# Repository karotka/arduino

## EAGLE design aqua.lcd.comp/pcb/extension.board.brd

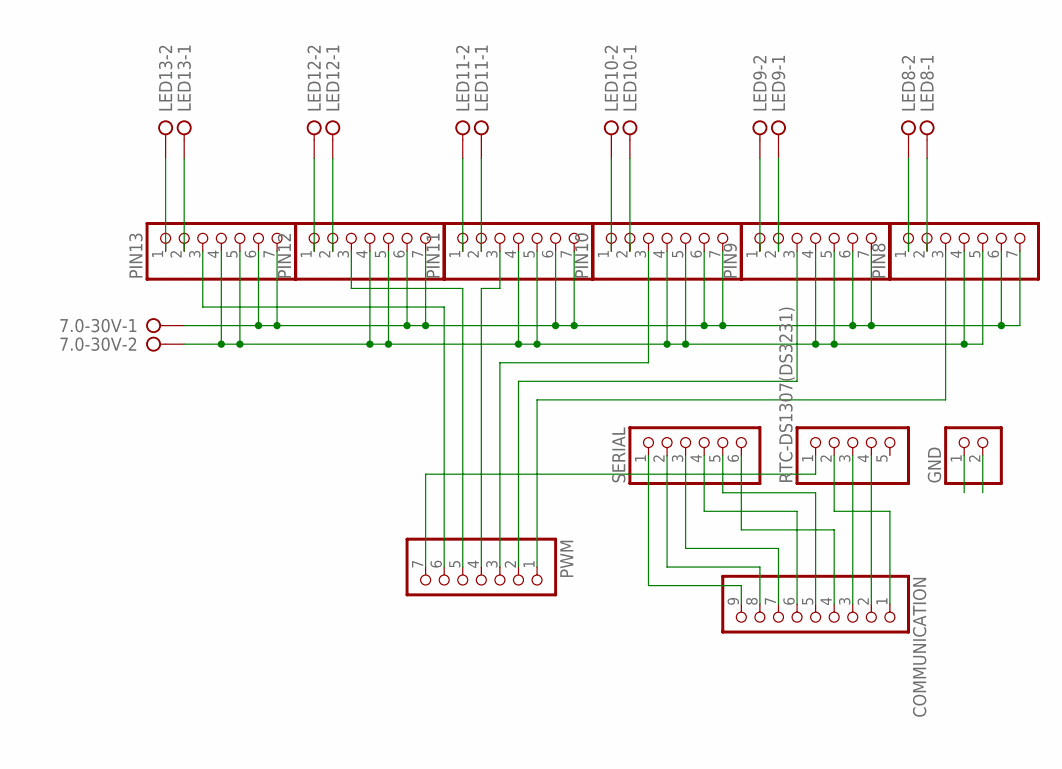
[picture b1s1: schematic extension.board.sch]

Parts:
7.0-30V: W237-02P; W237-132
COMMUNICATION: PINHD-1X9; 1X09
GND: PINHD-1X2; 1X02
LED8, LED9, LED10, LED11, LED12, LED13: W237-02P; W237-132
PIN8, PIN9, PIN10, PIN11, PIN12, PIN13: PINHD-1X7; 1X07
PWM: PINHD-1X7; 1X07
RTC-DS1307(DS3231): PINHD-1X5; 1X05
SERIAL: PINHD-1X6; 1X06

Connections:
GND: 7.0-30V.2, GND.1, PIN8.4, PIN8.5, PIN9.4, PIN9.5, PIN10.4, PIN10.5, PIN11.4, PIN11.5, PIN12.4, PIN12.5, PIN13.4, PIN13.5, PWM.7, RTC-DS1307(DS3231).1
unnamed: COMMUNICATION.2, RTC-DS1307(DS3231).4
unnamed: COMMUNICATION.3, RTC-DS1307(DS3231).3
unnamed: COMMUNICATION.4, SERIAL.6
unnamed: COMMUNICATION.5, SERIAL.5
unnamed: PIN8.3, PWM.1
unnamed: PIN9.3, PWM.2
unnamed: PIN10.3, PWM.3
unnamed: PIN11.3, PWM.4
unnamed: PIN12.3, PWM.5
unnamed: PIN13.3, PWM.6
unnamed: LED8.1, PIN8.2
unnamed: LED8.2, PIN8.1
unnamed: LED9.1, PIN9.2
unnamed: LED9.2, PIN9.1
unnamed: LED10.1, PIN10.2
unnamed: LED10.2, PIN10.1
unnamed: LED11.1, PIN11.2
unnamed: LED11.2, PIN11.1
unnamed: LED12.1, PIN12.2
unnamed: LED12.2, PIN12.1
unnamed: LED13.1, PIN13.2
unnamed: LED13.2, PIN13.1
unnamed: COMMUNICATION.6, SERIAL.4
unnamed: COMMUNICATION.7, SERIAL.3
unnamed: COMMUNICATION.8, SERIAL.2
unnamed: COMMUNICATION.9, SERIAL.1
VCC: COMMUNICATION.1, GND.2, RTC-DS1307(DS3231).2
VCC12: 7.0-30V.1, PIN8.6, PIN8.7, PIN9.6, PIN9.7, PIN10.6, PIN10.7, PIN11.6, PIN11.7, PIN12.6, PIN12.7, PIN13.6, PIN13.7

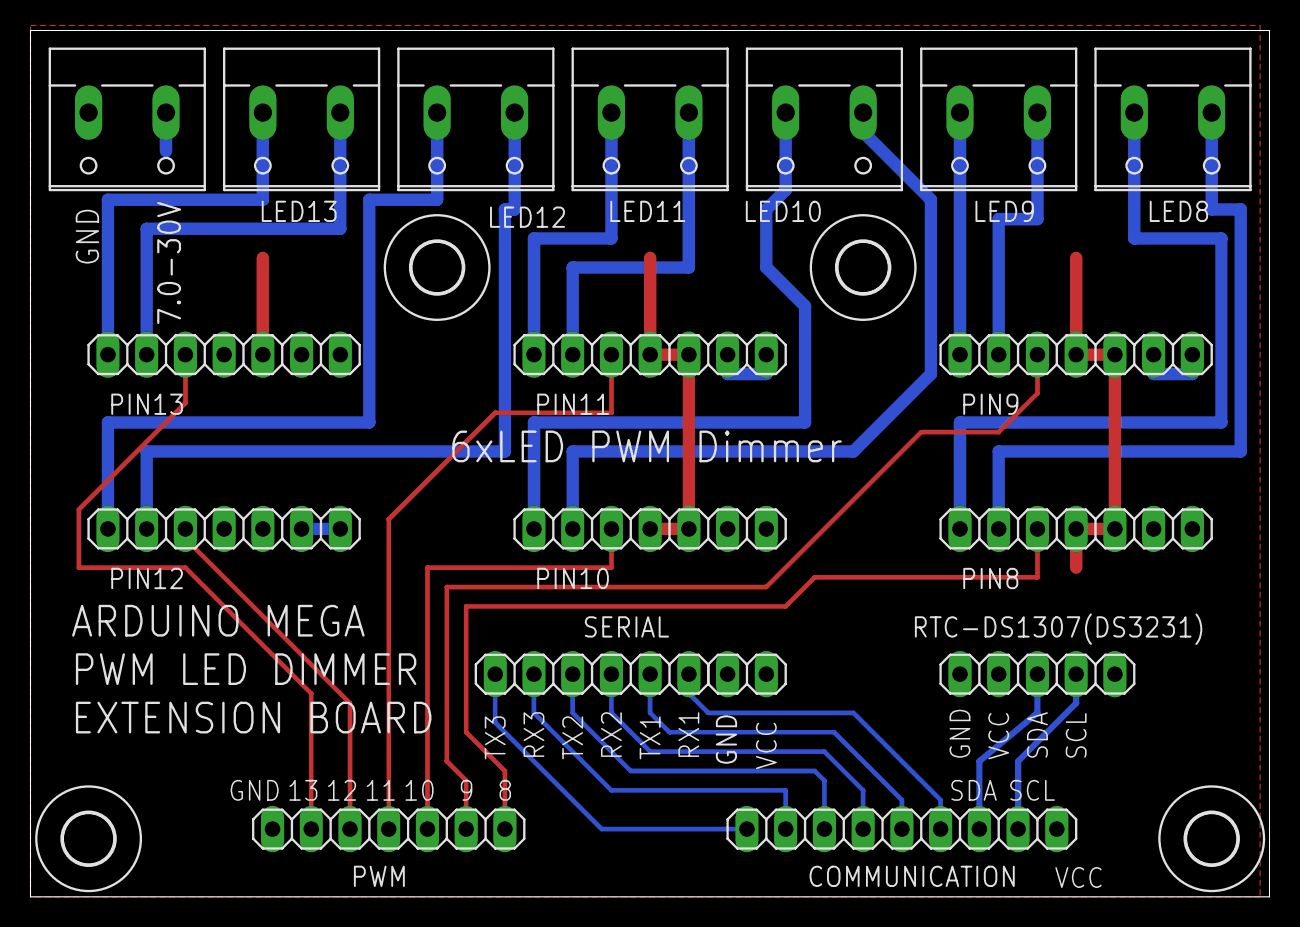
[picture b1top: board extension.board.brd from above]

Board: 2 copper layers, 81.3 x 56.8 mm, 22 parts (0 on the bottom side), 29 nets.

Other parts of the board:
U$1, U$2, U$3, U$4: 3,3

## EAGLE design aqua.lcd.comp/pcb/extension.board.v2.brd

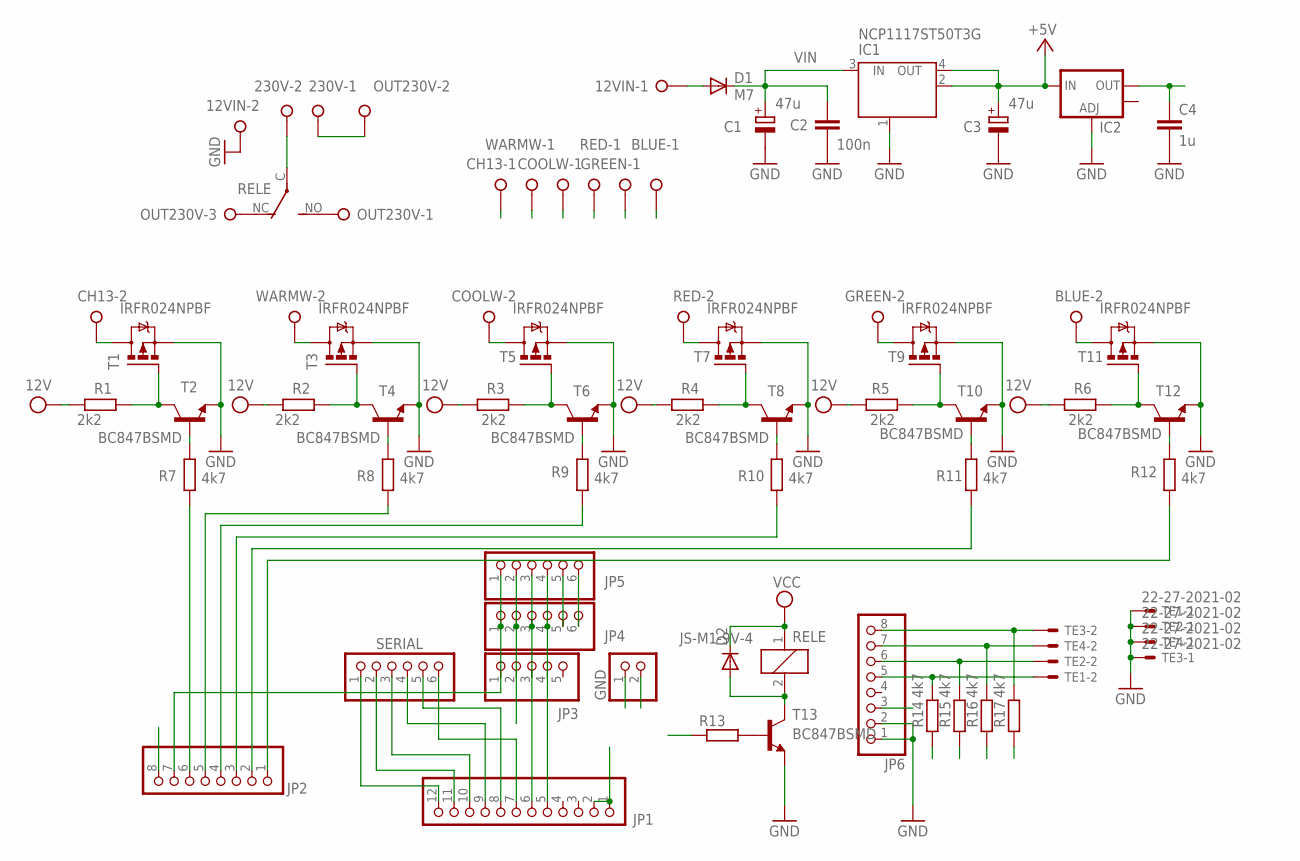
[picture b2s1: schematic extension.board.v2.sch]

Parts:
12VIN, 230V: W237-02P; W237-132
BLUE: W237-02P; W237-132
C1, C3: 47u; PANASONIC_D
C2: 100n; C1206
C4: 1u; C0805
CH13: W237-02P; W237-132
COOLW: W237-02P; W237-132
D1: M7; SMB
D2: DIODE-DO-214AC; DO-214AC
GND: PINHD-1X2; 1X02
GREEN: W237-02P; W237-132
IC1: NCP1117ST50T3G; SOT223
IC2: V_REG_LM1117SOT223; SOT223
JP1: PINHD-1X12; 1X12
JP2, JP6: PINHD-1X8; 1X08
JP3: PINHD-1X5; 1X05
JP4, JP5: PINHD-1X6; 1X06
OUT230V: W237-3E
R1, R2, R3, R4, R5, R6: 2k2; R1206
R7, R8, R9, R10, R11, R12, R14, R15, R16, R17: 4k7; R1206
R13: R-EU_0207/15; 0207/15
RED: W237-02P; W237-132
RELE: JS-M1-9V-4; JS-M
SERIAL: PINHD-1X6; 1X06
T1, T3, T5, T7, T9, T11: IRFR024NPBF; D-PAK_TO252AA
T2, T4, T6, T8, T10, T12, T13: BC847BSMD; SOT23
TE1, TE2, TE3, TE4: 22-27-2021-02; 6410-02
WARMW: W237-02P; W237-132

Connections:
3.3V: C4.1, IC2.2 (OUT), JP2.8, JP3.2, JP4.2, JP5.2, R14.2, R15.2, R16.2, R17.2
+5V: C3.+, D2.C, GND.2, IC1.2 (OUT), IC1.4 (OUT), IC2.3 (IN), JP1.1, JP1.2, RELE.1
GND: 12VIN.2, C1.-, C2.2, C3.-, C4.2, GND.1, IC1.1 (GND/ADJ), IC2.1 (ADJ), JP2.7, JP3.1, JP4.1, JP5.1, JP6.1, JP6.2, T1.3 (S), T2.2 (E), T3.3 (S), T4.2 (E), T5.3 (S), T6.2 (E), T7.3 (S), T8.2 (E), T9.3 (S), T10.2 (E), T11.3 (S), T12.2 (E), T13.2 (E), TE1.1, TE2.1, TE3.1, TE4.1
unnamed: 230V.1, OUT230V.2
unnamed: 230V.2, RELE.C
unnamed: JP1.7, SERIAL.6
unnamed: JP1.8, SERIAL.5
unnamed: JP2.1, R12.2
unnamed: JP2.2, R11.2
unnamed: JP2.3, R10.2
unnamed: JP2.4, R9.2
unnamed: JP2.5, R8.2
unnamed: JP2.6, R7.2
unnamed: R7.1, T2.1 (B)
unnamed: R1.2, T1.1 (G), T2.3 (C)
unnamed: CH13.2, T1.4 (D)
unnamed: OUT230V.1, RELE.NO (S)
unnamed: R8.1, T4.1 (B)
unnamed: R2.2, T3.1 (G), T4.3 (C)
unnamed: T3.4 (D), WARMW.2
unnamed: R9.1, T6.1 (B)
unnamed: R3.2, T5.1 (G), T6.3 (C)
unnamed: COOLW.2, T5.4 (D)
unnamed: R10.1, T8.1 (B)
unnamed: R4.2, T7.1 (G), T8.3 (C)
unnamed: JP1.9, SERIAL.4
unnamed: JP1.10, SERIAL.3
unnamed: JP1.11, SERIAL.2
unnamed: JP6.8, R17.1, TE3.2
unnamed: RED.2, T7.4 (D)
unnamed: R11.1, T10.1 (B)
unnamed: R5.2, T9.1 (G), T10.3 (C)
unnamed: GREEN.2, T9.4 (D)
unnamed: R12.1, T12.1 (B)
unnamed: R6.2, T11.1 (G), T12.3 (C)
unnamed: BLUE.2, T11.4 (D)
unnamed: R13.2, T13.1 (B)
unnamed: OUT230V.3, RELE.NC (O)
unnamed: JP6.7, R16.1, TE4.2
unnamed: D2.A, RELE.2, T13.3 (C)
unnamed: JP6.5, R14.1, TE1.2
unnamed: JP6.6, R15.1, TE2.2
unnamed: JP4.5, JP5.5
unnamed: JP4.6, JP5.6
PWRIN: 12VIN.1, BLUE.1, CH13.1, COOLW.1, D1.A, GREEN.1, RED.1, WARMW.1
SCL: JP1.5, JP3.4, JP4.4, JP5.4
SDA: JP1.6, JP3.3, JP4.3, JP5.3
TX3: JP1.12, R13.1, SERIAL.1
VIN: C1.+, C2.1, D1.C, IC1.3 (IN), JP6.3, R1.1, R2.1, R3.1, R4.1, R5.1, R6.1

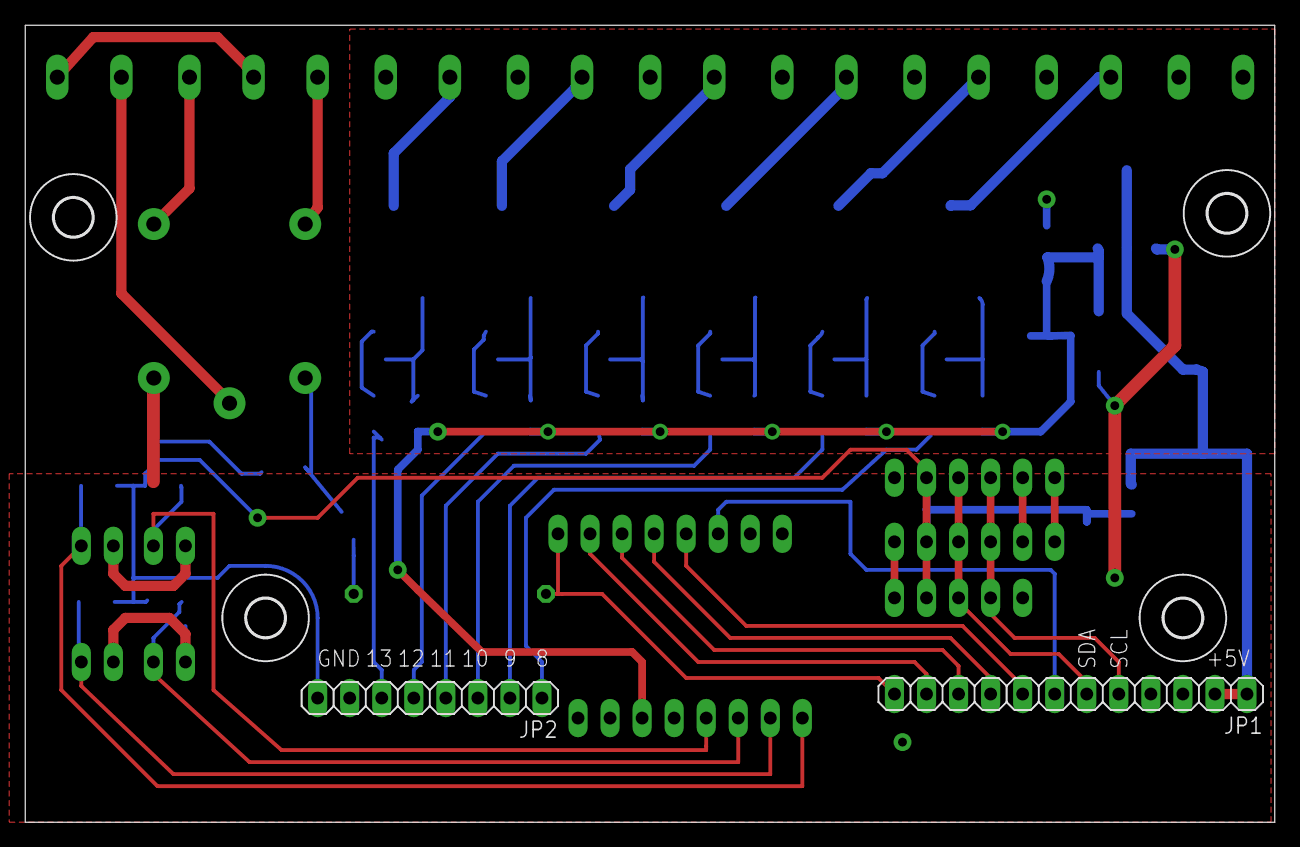
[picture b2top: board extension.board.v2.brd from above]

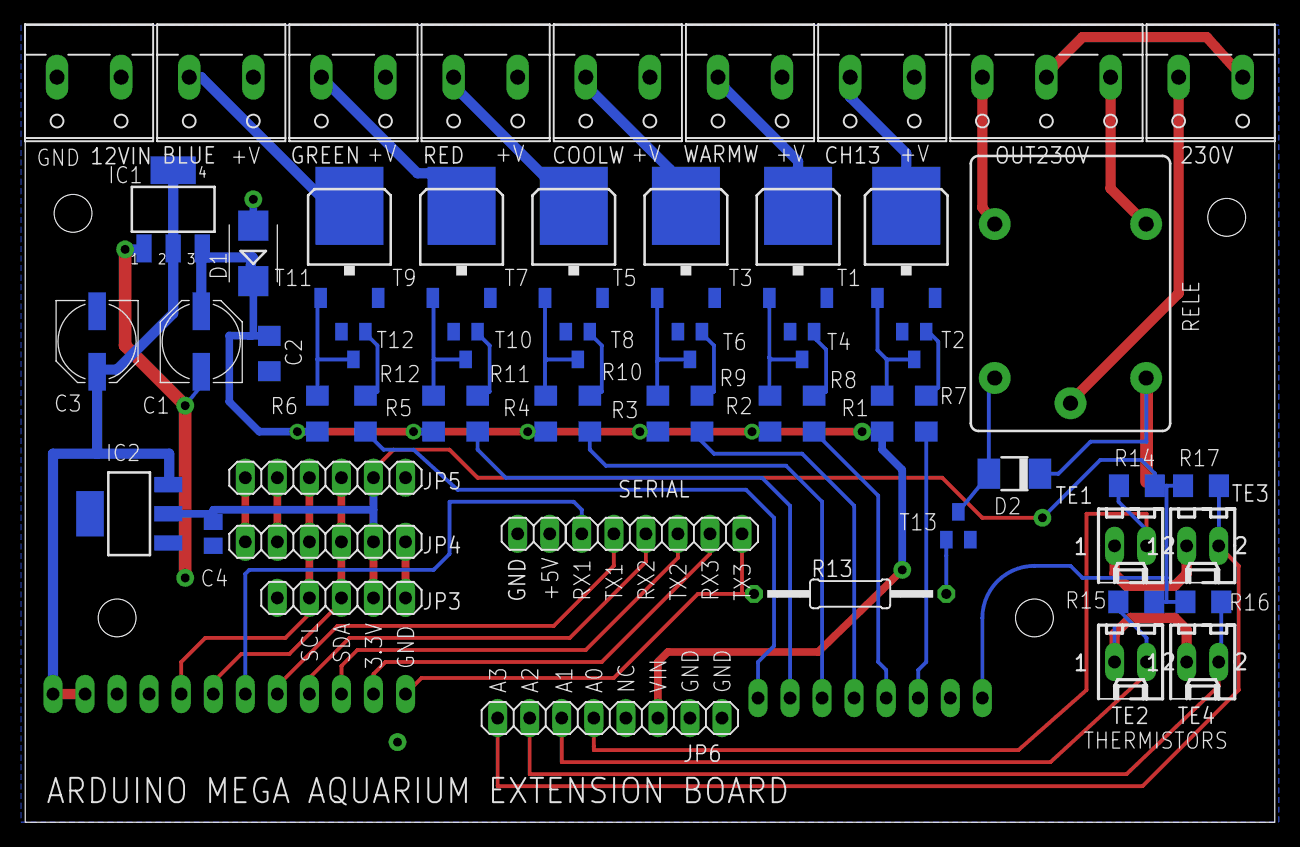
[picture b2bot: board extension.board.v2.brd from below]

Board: 2 copper layers, 99.0 x 63.2 mm, 64 parts (58 on the bottom side), 49 nets.

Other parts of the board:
U$1, U$2, U$3, U$4: 3,0

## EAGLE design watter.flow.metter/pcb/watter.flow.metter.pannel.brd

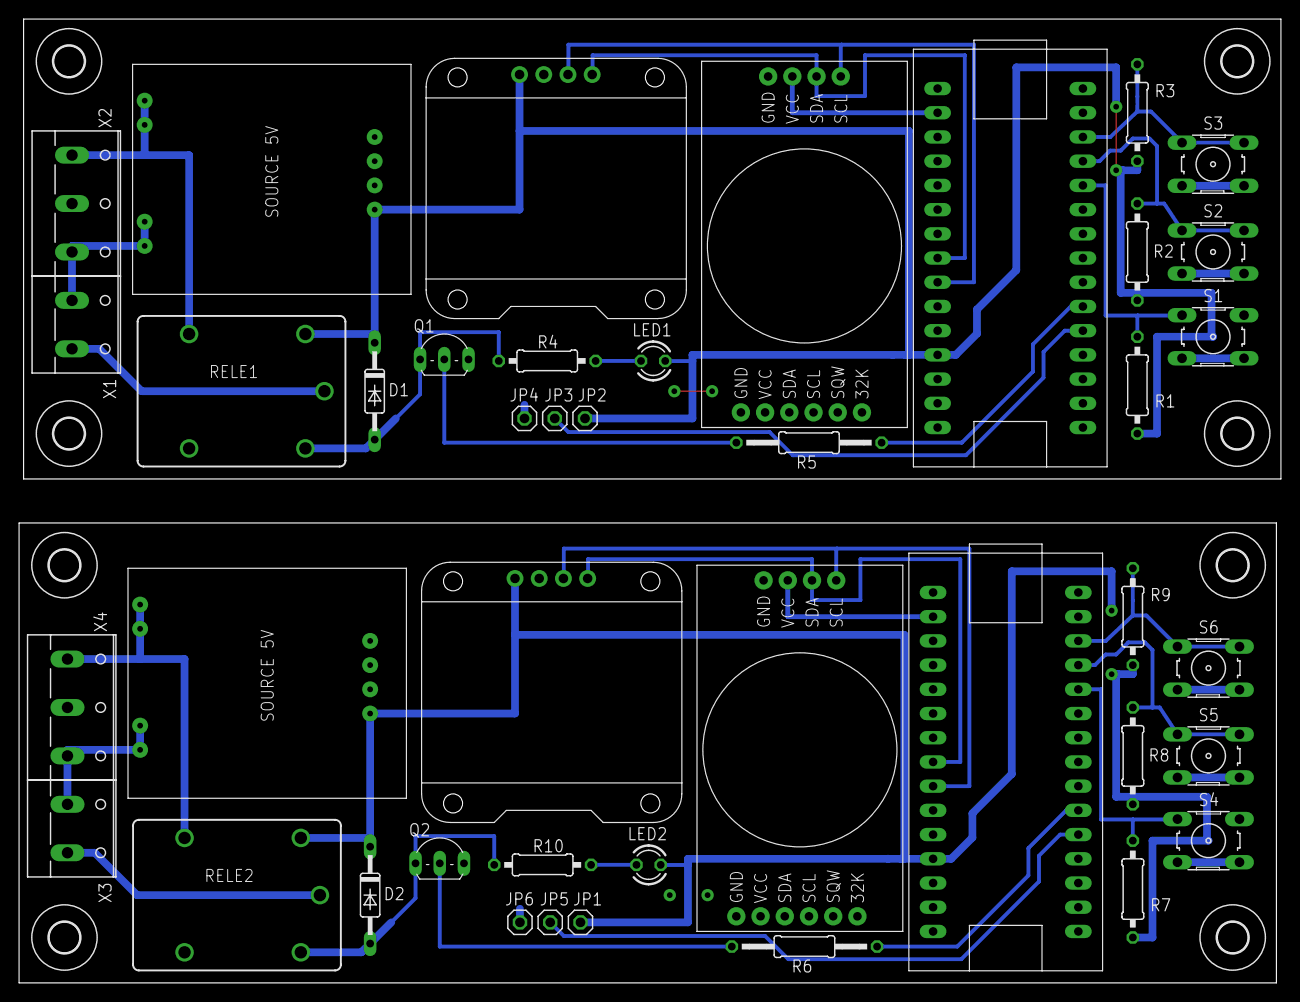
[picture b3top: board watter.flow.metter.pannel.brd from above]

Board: 2 copper layers, 132.4 x 101.1 mm, 50 parts (0 on the bottom side), 32 nets.

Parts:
D1, D2: 1N4148DO35-10; DO35-10
DISPLAY, DISPLAY1: OLED_0.96_I2C
JP1, JP2, JP3, JP4, JP5, JP6: 1X01
LED1, LED2: LED3MM
Q1, Q2: BC546A; TO92-EBC
R1, R2, R3, R4, R7, R8, R9, R10: 0207/10
R5, R6: 0207/15
RELE1, RELE2: JS-M1-9V-4; JS-M
S1, S2, S3, S4, S5, S6: B3F-10XX
U$1, U$5: NANO
U$2, U$10: PWR5V; SUPP
U$3, U$4, U$7, U$8, U$11, U$12, U$13, U$14: 3,2
U$6, U$9: DS3231BOARD; BOARD
X1, X3: W237-132
X2, X4: W237-3E

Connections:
3.3V: U$5.3.3V, U$6.VCC@2
3.3V1: U$1.3.3V, U$9.VCC@2
D1: JP5.1, U$1.D2
D2: JP3.1, U$5.D2
D3: R5.1, U$5.D3
D4: R6.1, U$1.D3
GND: DISPLAY.GND, JP4.1, Q1.E, S1.3, S1.4, S2.3, S2.4, S3.3, S3.4, U$2.P$5, U$5.GND, U$6.GND@1, U$6.GND@2
GND1: DISPLAY1.GND, JP6.1, Q2.E, S4.3, S4.4, S5.3, S5.4, S6.3, S6.4, U$1.GND, U$9.GND@1, U$9.GND@2, U$10.P$5
unnamed: RELE1.C, X1.2
unnamed: R1.1, S1.1, S1.2, U$5.D8
unnamed: U$2.P$3, U$2.P$4, X1.1, X2.3
unnamed: RELE1.NO, U$2.P$1, U$2.P$2, X2.1
unnamed: R2.1, S2.1, S2.2, U$5.D9
unnamed: R3.1, S3.1, S3.2, U$5.D10
unnamed: Q1.B, R5.2
unnamed: LED1.K, R4.2
unnamed: D2.A, Q2.C, R10.1, RELE2.2
unnamed: U$10.P$3, U$10.P$4, X3.1, X4.3
unnamed: RELE2.NO, U$10.P$1, U$10.P$2, X4.1
unnamed: RELE2.C, X3.2
unnamed: R7.1, S4.1, S4.2, U$1.D8
unnamed: R8.1, S5.1, S5.2, U$1.D9
unnamed: R9.1, S6.1, S6.2, U$1.D10
unnamed: Q2.B, R6.2
unnamed: LED2.K, R10.2
unnamed: D1.A, Q1.C, R4.1, RELE1.2
SCL: DISPLAY.SCL, U$5.A5, U$6.SCL@2
SCL1: DISPLAY1.SCL, U$1.A5, U$9.SCL@2
SDA: DISPLAY.SDA, U$5.A4, U$6.SDA@2
SDA1: DISPLAY1.SDA, U$1.A4, U$9.SDA@2
VCC: D1.C, DISPLAY.VCC, JP2.1, LED1.A, R1.2, R2.2, R3.2, RELE1.1, U$2.P$8, U$5.5V, U$6.VCC@1
VCC1: D2.C, DISPLAY1.VCC, JP1.1, LED2.A, R7.2, R8.2, R9.2, RELE2.1, U$1.5V, U$9.VCC@1, U$10.P$8

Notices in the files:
parts and their libraries:
sparkfun: Licensing: CC v3.0 Share-Alike You are welcome to use this library for commercial purposes.
